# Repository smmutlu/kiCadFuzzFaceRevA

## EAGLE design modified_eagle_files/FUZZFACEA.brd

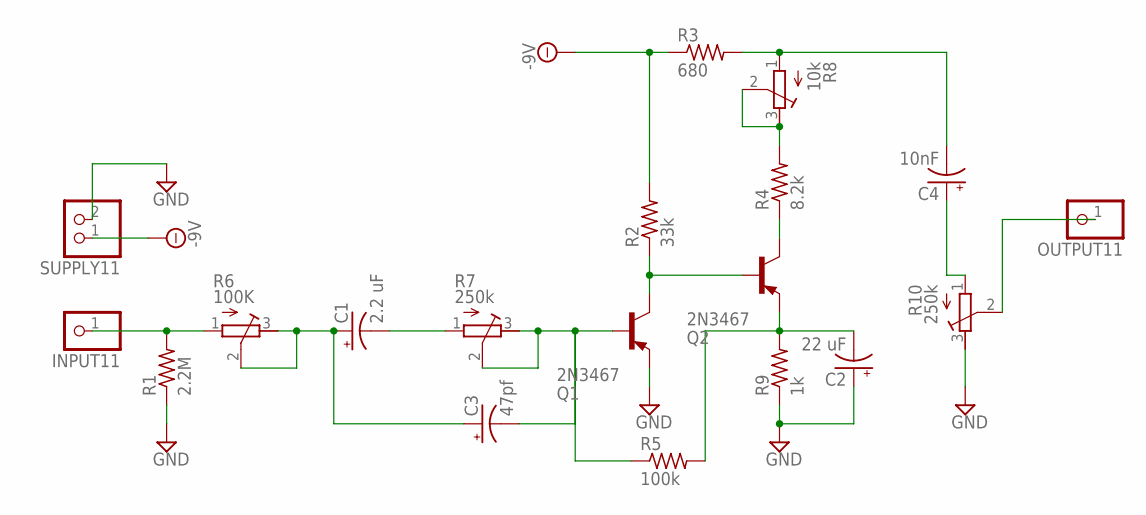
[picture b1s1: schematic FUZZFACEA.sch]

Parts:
C1: 2.2 uF; TAP5-60
C2: 22 uF; TAP5-60
C3: 47pf; E2-4
C4: 10nF; E15-6
INPUT11: PINHD-1X1; 1X01
OUTPUT11: PINHD-1X1; 1X01
Q1, Q2: 2N3467; TO39
R1: 2.2M; 0411/12
R2: 33k; 0411/12
R3: 680; 0411/12
R4: 8.2k; 0411/12
R5: 100k; 0411/12
R6: 100K; RTRIM64X
R7, R10: 250k; RTRIM64X
R8: 10k; RTRIM64X
R9: 1k; 0411/12
SUPPLY11: PINHD-1X2; 1X02

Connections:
-9V: R2.2, R3.1, SUPPLY11.1
GND: C2.+, Q1.1 (E), R1.1, R9.1, R10.3 (E), SUPPLY11.2
INPUT: INPUT11.1, R1.2, R6.1 (A)
N1: C1.+, C3.+, R6.2 (S), R6.3 (E)
N2: C1.-, R7.1 (A)
N3: C3.-, Q1.2 (B), R5.1, R7.2 (S), R7.3 (E)
N4: C2.-, Q2.1 (E), R5.2, R9.2
N5: Q1.3 (C), Q2.2 (B), R2.1
N6: Q2.3 (C), R4.1
N7: R4.2, R8.2 (S), R8.3 (E)
N8: C4.-, R3.2, R8.1 (A)
N9: C4.+, R10.1 (A)
OUTPUT: OUTPUT11.1, R10.2 (S)

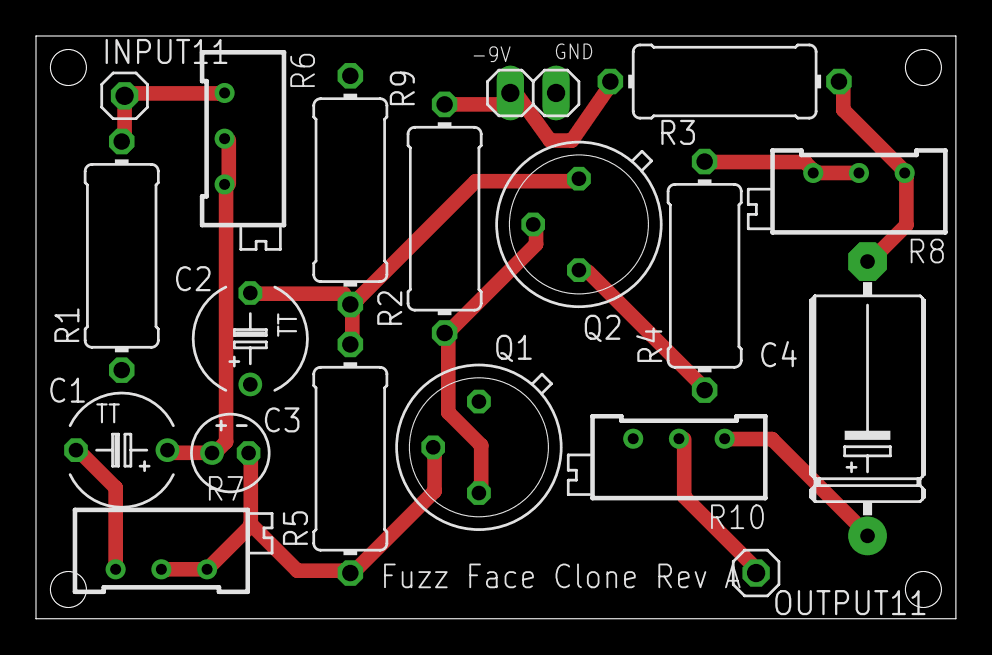
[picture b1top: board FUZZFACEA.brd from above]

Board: 2 copper layers, 51.1 x 32.4 mm, 19 parts (0 on the bottom side), 13 nets.

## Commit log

2018-04-14 Init
